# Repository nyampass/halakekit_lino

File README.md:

# HaLakeKitLino
A BLE module.

# PCB
## Software
This PCB was designed on KiCad.

## components
- [MDBT40](http://www.tinyosshop.com/index.php?route=product/product&product_id=970)
- [NJM287033](http://akizukidenshi.com/catalog/g/gI-10393/)
- [RTF015N03](http://akizukidenshi.com/catalog/g/gI-05959/)
- [BAT-HLD-001](http://www.digikey.jp/product-detail/ja/linx-technologies-inc/BAT-HLD-001-TR/BAT-HLD-001-TRCT-ND/5803803)
- [32.7Hz cristal](http://akizukidenshi.com/catalog/g/gP-07195/)
- 4.7uf condensor
- 0.1uf condensor
- 0.01uf condensor
- 12pf condensor * 2
- 1K resister * 2

Size of chip condensors and resisters are all 0603.

# License
MIT

# References
- [BLE nano](http://redbearlab.com/blenano/)
- [BLE nano schematic](https://github.com/RedBearLab/BLENano/tree/master/PCB)
- [KiCAD_Libraries/PCB/RF_Modules.pretty/MDBT40.kicad_mod](https://github.com/CascoLogix/KiCAD_Libraries/blob/master/PCB/RF_Modules.pretty/MDBT40.kicad_mod)

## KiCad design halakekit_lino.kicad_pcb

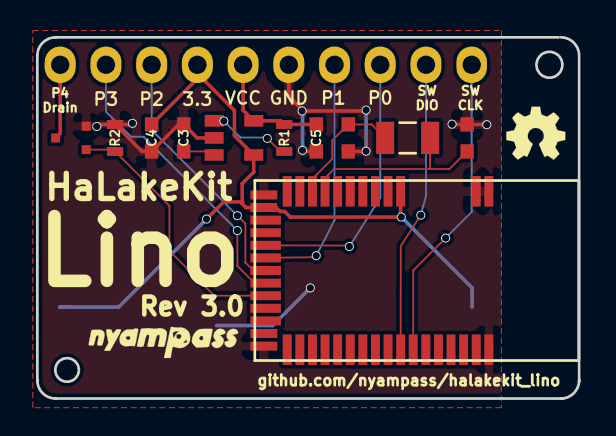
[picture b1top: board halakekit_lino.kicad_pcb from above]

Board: 2 copper layers, 30.1 x 20.1 mm, 13 parts (1 on the bottom side), 15 nets.

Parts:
BT1: Battery; BAT-HLD-001-TRCT
C1, C2: 12pf; C_0603
C3: 0.01uf; C_0603
C4: 4.7uf1; C_0603
C5: 0.1uf1; C_0603
J1: HEADER_10; Pin_Header_Straight_1x10
R1, R2: 1K; R_0603
U1: MDBT40
U2: NJM2870; SOT-23-5
U3: RTF015N03; rtf015n03
Y1: Crystal; FC-135

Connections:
+3V3: BT1.1, C4.1, J1.7, U1.3, U1.14, U2.4
GND: BT1.2, C1.2, C2.2, C3.2, C4.2, C5.2, J1.5, R2.2, U1.1, U1.2, U1.13, U1.25, U1.42, U2.2, U3.2
unnamed: C1.1, U1.9, Y1.2
unnamed: C2.1, U1.10, Y1.1
unnamed: C3.1, U2.3
unnamed: R1.2, U2.1
P0: J1.3, U1.17
P1: J1.4, U1.18
P2: J1.8, U1.19
P3: J1.9, U1.20
P4: R2.1, U1.21, U3.1
P4_Drain: J1.10, U3.3
SWDCLK: J1.1, U1.36
SWDIO: J1.2, U1.35
VCC: C5.1, J1.6, R1.1, U2.5

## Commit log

2016-12-08 Updated to ver1.1
2016-12-26 Add files to order PCBA for elecrow
2016-12-27 Change board layout as rev 1.2
2016-12-27 Update plot data to order Rev2.0 PCB
2016-12-27 Add docs
2016-12-27 Add readme
2016-12-30 Add MIT license
2017-01-09 Create net data with using MDBT40
2017-01-10 Change url on pcb
2017-01-10 Created pcb directory
2017-01-10 Update docs
2017-01-10 Update plot files to order
2017-01-11 Add links for pcb components on readme
2017-01-12 Correct path for image on readme
2017-02-11 Update silk
2020-05-25 Update something
2020-05-25 Correct typo about resister
